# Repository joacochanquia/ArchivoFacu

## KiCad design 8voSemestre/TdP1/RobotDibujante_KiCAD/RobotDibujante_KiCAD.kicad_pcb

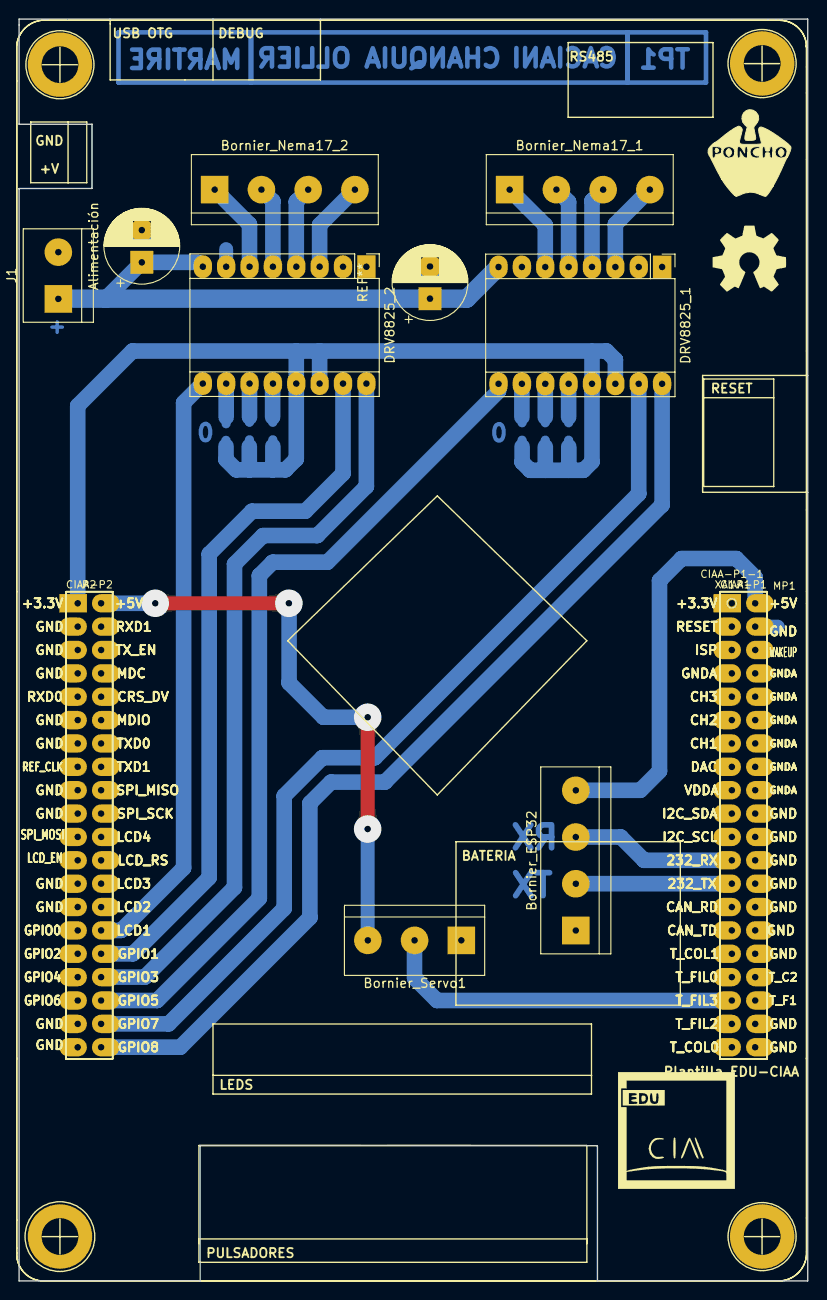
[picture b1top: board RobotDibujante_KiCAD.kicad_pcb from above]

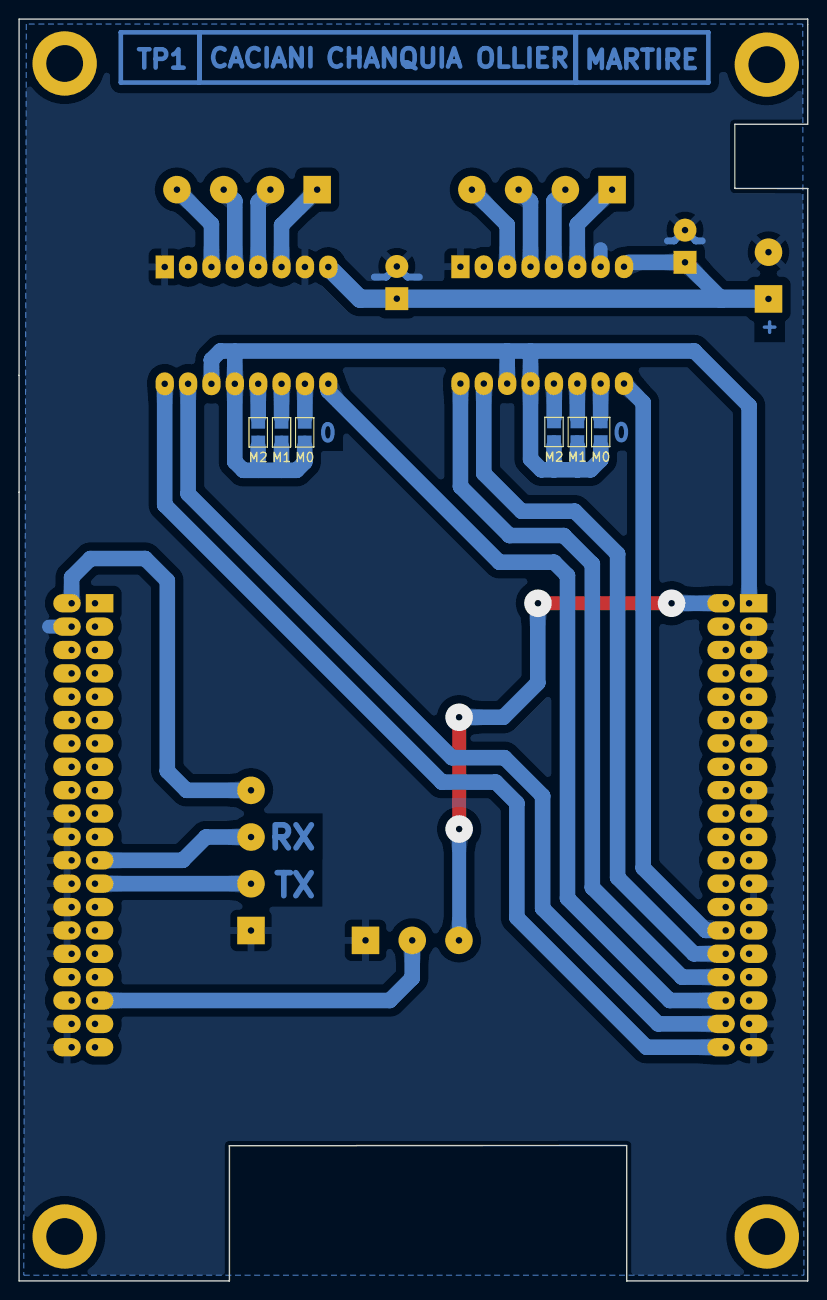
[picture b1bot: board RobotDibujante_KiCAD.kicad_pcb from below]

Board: 2 copper layers, 85.7 x 137.2 mm, 19 parts (6 on the bottom side), 28 nets.

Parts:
Alimentación: CP_Radial_D8.0mm_P3.50mm
Bornier_ESP32: Screw_Terminal_01x04; TerminalBlock_bornier-4_P5.08mm
Bornier_Nema17_1, Bornier_Nema17_2: Screw_Terminal_01x04; TerminalBlock_bornier-4_P5.08mm
Bornier_Servo1: Screw_Terminal_01x03; TerminalBlock_bornier-3_P5.08mm
CIAA-P1-1: Conn_02x20_Odd_Even; Tira_P1_CIAA
CIAA-P2-1: Conn_02x20_Odd_Even; Tira_P2_CIAA
DRV8825_1, DRV8825_2: Pololu_Breakout_DRV8825; Pololu_Breakout-16_15.2x20.3mm
G101: Logo_OSHWA
J1: Screw_Terminal_01x02; TerminalBlock_bornier-2_P5.08mm
M0, M1, M1#2, M2, M2#2: SMD Solder Jumper, 1x1.5mm Pads, 0.75mm gap, open
M0#2: SMD Solder Jumper, 1x1.5mm Pads, 0.75mm gap, open; SMD Solder Jumper, 1x1.5mm Pads, 0.9mm gap, open
MP1: Plantilla_EDU-CIAA
XA1: poncho_grande

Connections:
3V3L: CIAA-P2-1.1 (3V3), DRV8825_1.13 (~RST), DRV8825_1.14 (~SLP), DRV8825_2.13 (~RST), DRV8825_2.14 (~SLP), M0.1, M0#2.1, M1.1, M1#2.1, M2.1, M2#2.1
5VL: Bornier_Servo1.3, CIAA-P2-1.2 (5V)
5VR: Bornier_ESP32.4, CIAA-P1-1.2 (5V)
A1_1: Bornier_Nema17_1.3, DRV8825_1.4 (A1)
A1_2: Bornier_Nema17_2.3, DRV8825_2.4 (A1)
A2_1: Bornier_Nema17_1.4, DRV8825_1.3 (A2)
A2_2: Bornier_Nema17_2.4, DRV8825_2.3 (A2)
B1_1: Bornier_Nema17_1.2, DRV8825_1.5 (B1)
B1_2: Bornier_Nema17_2.2, DRV8825_2.5 (B1)
B2_1: Bornier_Nema17_1.1, DRV8825_1.6 (B2)
B2_2: Bornier_Nema17_2.1, DRV8825_2.6 (B2)
DIR1: CIAA-P2-1.40 (GPIO8), DRV8825_1.16 (DIR)
DIR2: CIAA-P2-1.34 (GPIO3), DRV8825_2.16 (DIR)
EN1: CIAA-P2-1.36 (GPIO5), DRV8825_1.9 (~EN)
EN2: CIAA-P2-1.30 (LCD1), DRV8825_2.9 (~EN)
GND: Alimentación.2, Bornier_ESP32.1, Bornier_Servo1.1, CIAA-P1-1.4 (GND), CIAA-P1-1.20 (GND), CIAA-P1-1.22 (GND), CIAA-P1-1.24 (GND), CIAA-P1-1.26 (GND), CIAA-P1-1.28 (GND), CIAA-P1-1.30 (GND), CIAA-P1-1.32 (GND), CIAA-P1-1.38 (GND), CIAA-P1-1.40 (GND), CIAA-P2-1.3 (GND), CIAA-P2-1.5 (GND), CIAA-P2-1.7 (GND), CIAA-P2-1.11 (GND), CIAA-P2-1.13 (GND), CIAA-P2-1.17 (GND), CIAA-P2-1.19 (GND), CIAA-P2-1.25 (GND), CIAA-P2-1.27 (GND), CIAA-P2-1.37 (GND), CIAA-P2-1.39 (GND), DRV8825_1.1 (GND), DRV8825_1.7 (GND), DRV8825_2.1 (GND), DRV8825_2.7 (GND), J1.2
M01: DRV8825_1.10 (M0), M0.2
M02: DRV8825_2.10 (M0), M0#2.2
M11: DRV8825_1.11 (M1), M1.2
M12: DRV8825_2.11 (M1), M1#2.2
M21: DRV8825_1.12 (M2), M2.2
M22: DRV8825_2.12 (M2), M2#2.2
RS232_RX: Bornier_ESP32.3, CIAA-P1-1.23 (RS232_RX)
RS232_TX: Bornier_ESP32.2, CIAA-P1-1.25 (RS232_TX)
STEP1: CIAA-P2-1.38 (GPIO7), DRV8825_1.15 (STEP)
STEP2: CIAA-P2-1.32 (GPIO1), DRV8825_2.15 (STEP)
TFIL3: Bornier_Servo1.2, CIAA-P1-1.35 (TFIL3)
VMOT: Alimentación.1, DRV8825_1.8 (VMOT), DRV8825_2.8 (VMOT), J1.1

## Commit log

2024-06-14 Semestres 3-6
2024-06-14 Practica10TdA
2025-02-24 EcoYEmp
2025-02-24 CDyM
2025-02-24 AAP (DeepLearning)
2025-02-24 Redes2
2025-03-18 TdP1
2025-04-29 Aspectos28/4/25
2025-04-29 DSA28/4/25
2025-04-29 Electro2_28/4/25
2025-04-29 SDyP28/4/25
2025-05-02 Actualización2/5/25
2025-05-02 ActAspectos2/5/25
2025-05-07 ActWindows7/5/25
2025-05-07 ActLinux7/5/25
2025-08-03 ActDSA_SDyP - eliminados archivos grandes (rockyous)
2025-08-26 AL-fin
2025-08-26 DSA-fin
2025-08-26 Electro2-fin
2025-08-26 SDyP-fin
2025-08-26 10moSemestre
2025-09-03 Redaccion3/9
2025-09-05 Redaccion4/9
2025-09-10 Redaccion10/9
2025-09-13 TdP2-13/9
2025-09-16 Redaccion16/9
2025-09-24 DSA-internacional
2025-09-24 Redaccion23/9
2025-10-02 DE02/10
2025-10-02 TdP02/10
2025-10-03 Redaccion02/10
2025-10-03 DEWin02/10
2025-10-13 TdP2 13/10
2025-10-22 22/10
2025-10-22 DE22/10
2025-10-22 Redaccion22/10
2025-10-23 PPS e InformeAvance22/10
2025-10-25 Redaccion25/10
2025-11-11 11/11
2025-11-30 30/11
2025-12-02 2/12
